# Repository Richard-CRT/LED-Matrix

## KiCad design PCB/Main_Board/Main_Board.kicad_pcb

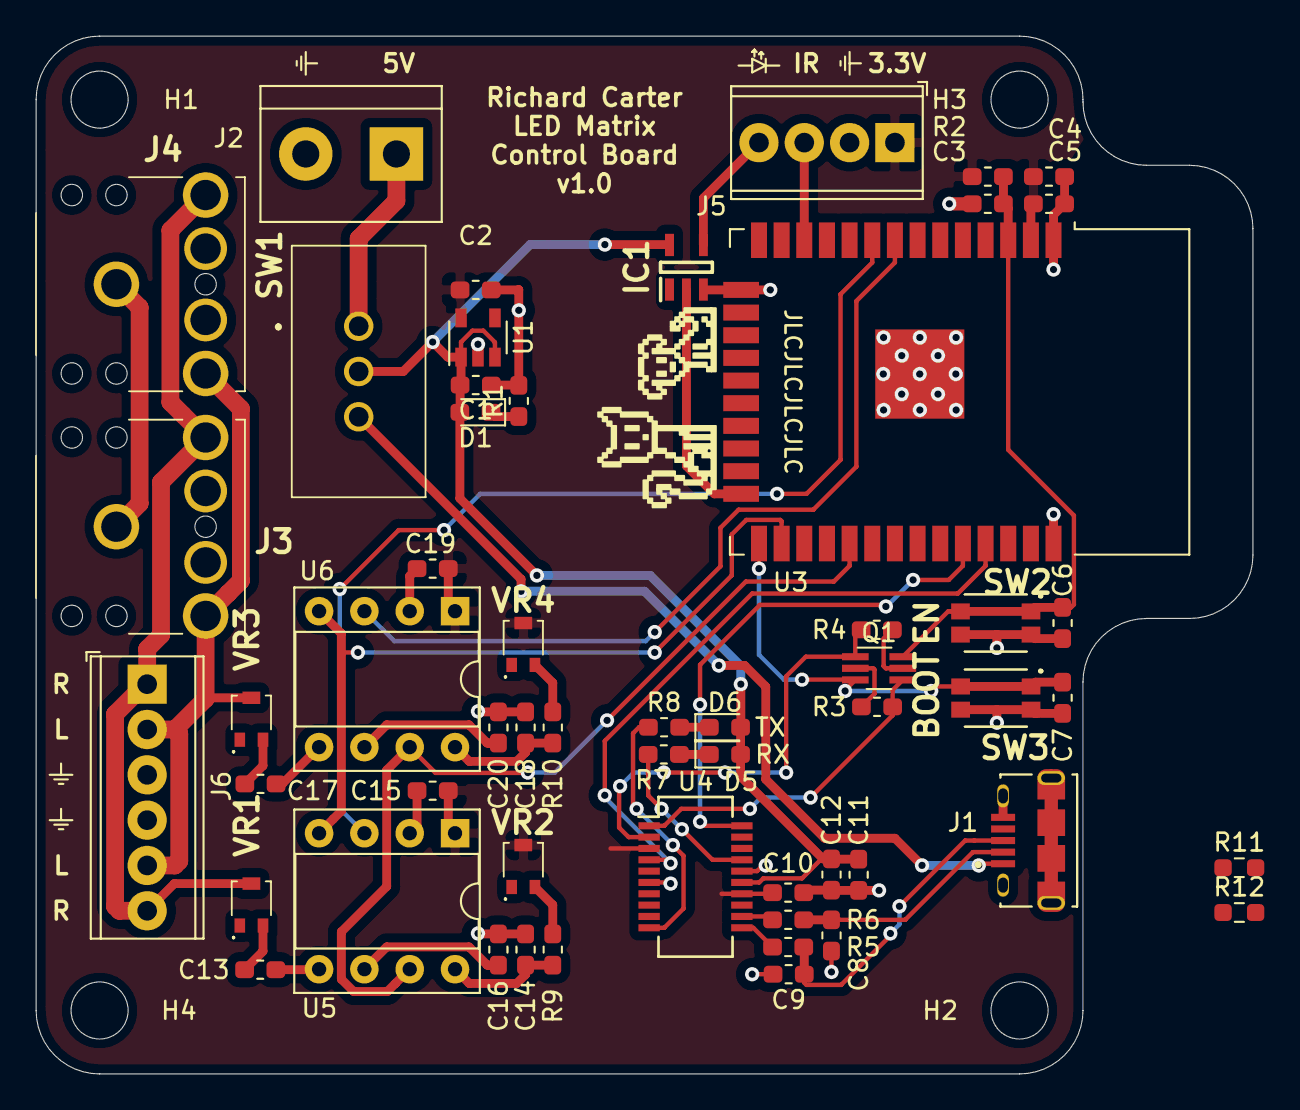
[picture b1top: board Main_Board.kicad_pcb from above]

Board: 2 copper layers, 68.2 x 58.2 mm, 61 parts (0 on the bottom side), 43 nets.

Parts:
ART1: Artwork; dog_2_small
ART2: Artwork; cat_small_mirrored
C1, C2, C3: 10uF; C_0603_1608Metric_Pad1.05x0.95mm_HandSolder
C4: 22uF; C_0603_1608Metric_Pad1.05x0.95mm_HandSolder
C5, C6, C7, C10, C11, C15, C16, C19, C20: 0.1uF; C_0603_1608Metric_Pad1.05x0.95mm_HandSolder
C8, C9: 47pF; C_0603_1608Metric_Pad1.05x0.95mm_HandSolder
C12: 4.7uF; C_0603_1608Metric_Pad1.05x0.95mm_HandSolder
C13, C17: 10nF; C_0603_1608Metric_Pad1.05x0.95mm_HandSolder
C14, C18: 33pF; C_0603_1608Metric_Pad1.05x0.95mm_HandSolder
D1: 5V_LED; LED_0603_1608Metric_Pad1.05x0.95mm_HandSolder
D5: RX_LED; LED_0603_1608Metric_Pad1.05x0.95mm_HandSolder
D6: TX_LED; LED_0603_1608Metric_Pad1.05x0.95mm_HandSolder
H1, H2, H3, H4: MountingHole; MountingHole_3.2mm_M3
IC1: 74LV1T34GVH; SOT95P275X110-5N
J1: USB_B_Micro; AMPHENOL_10118194-0001LF
J2: Screw_Terminal_01x02; TerminalBlock_bornier-2_P5.08mm
J3, J4: SJ1-3523N; SJ13523N
J5: Screw_Terminal_01x04; TerminalBlock_Phoenix_MPT-0,5-4-2.54_1x04_P2.54mm_Horizontal
J6: Screw_Terminal_01x06; TerminalBlock_Phoenix_MPT-0,5-6-2.54_1x06_P2.54mm_Horizontal
Q1: MBT3904DW1; SOT-363_SC-70-6_Handsoldering
R1, R7, R8: CUR_LIMIT_220R; R_0603_1608Metric_Pad1.05x0.95mm_HandSolder
R2: 47k; R_0603_1608Metric_Pad1.05x0.95mm_HandSolder
R3, R4: 10k; R_0603_1608Metric_Pad1.05x0.95mm_HandSolder
R5, R6: 27R; R_0603_1608Metric_Pad1.05x0.95mm_HandSolder
R9, R10: 180k; R_0603_1608Metric_Pad1.05x0.95mm_HandSolder
R11, R12: 1k; R_0603_1608Metric_Pad0.98x0.95mm_HandSolder
SW1: SW_SPDT; 25136NAH
SW2: EN; SKTHAHE010
SW3: BOOT; SKTHAHE010
U1: TLV75533PDBV; SOT-23-5
U3: ESP32-WROOM-32
U4: FT231XS; SSOP-20_3.9x8.7mm_P0.635mm
U5, U6: MSGEQ7; DIP-8_W7.62mm_Socket
VR1, VR2, VR3, VR4: TC42X-2-503E; TC42X2503E

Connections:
/+3.3V: C2.1, C4.1, C5.1, C10.2, C15.1, C19.1, J5.1, R2.1, U1.5, U3.2, U4.3, U4.14, U5.1, U6.1, VR2.2, VR4.2
/+5V: C1.1, C11.1, C12.1, D1.2, D5.2, D6.2, IC1.5, SW1.2, U1.1, U1.3, U4.15
/+POW_5V: J2.1, SW1.1
/+USB_5V: J1.1, SW1.3
/AUDIO_L: J3.2, J4.2, J6.2, J6.5, VR3.2
/AUDIO_R: J3.3, J4.3, J6.1, J6.6, VR1.2
/D+: C9.1, J1.3, R5.2
/D-: C8.1, J1.2, R6.2
/ESP32_Circuit/EN: C3.2, C6.1, Q1.6, R2.2, SW2.1, U3.3
/ESP32_Circuit/IO0: C7.1, Q1.3, SW3.1, U3.25
/ESP32_Circuit/IO1_TXD0: R12.2, U3.35
/ESP32_Circuit/IO3_RXD0: R11.2, U3.34
/ESP32_Circuit/~DTR: Q1.4, R3.2, U4.1
/ESP32_Circuit/~RTS: Q1.1, R4.2, U4.2
/IR_SENSOR: J5.3, U3.12
/LED_OUT_3.3V: IC1.2, U3.24
/LED_OUT_5V: IC1.4, J5.4
/MSGEQ7_L_OUT: U3.8, U6.3
/MSGEQ7_RESET: U3.29, U5.7, U6.7
/MSGEQ7_R_OUT: U3.9, U5.3
/MSGEQ7_STROBE: U3.26, U5.4, U6.4
Earth: C1.2, C2.2, C3.1, C4.2, C5.2, C6.2, C7.2, C8.2, C9.2, C10.1, C11.2, C12.2, C14.2, C15.2, C16.2, C18.2, C19.2, C20.2, IC1.3, J1.5, J1.6, J2.2, J3.1, J4.1, J5.2, J6.3, J6.4, R1.2, SW2.2, SW3.2, U1.2, U3.1, U3.15, U3.38, U3.39, U4.6, U4.16, U5.2, U6.2
unnamed: C13.1, VR1.3
unnamed: C13.2, U5.5
unnamed: C14.1, R9.2, U5.8
unnamed: C16.1, U5.6
unnamed: C17.1, VR3.3
unnamed: C17.2, U6.5
unnamed: C18.1, R10.2, U6.8
unnamed: C20.1, U6.6
unnamed: D1.1, R1.1
unnamed: D5.1, R7.1
unnamed: D6.1, R8.1
unnamed: Q1.2, R3.1
unnamed: Q1.5, R4.1
unnamed: R5.1, U4.11
unnamed: R6.1, U4.12
unnamed: R7.2, U4.17
unnamed: R8.2, U4.10
unnamed: R9.1, VR2.3
unnamed: R10.1, VR4.3
unnamed: R11.1, U4.20
unnamed: R12.1, U4.4

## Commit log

2020-09-06 Added PCB project
2020-09-06 Add schematic
2020-09-06 Restructure file system
2020-09-06 Add IR circuit
2020-09-07 Further schematic work and footprint association
2020-09-07 Further sourcing on mouser
2020-09-08 PCB Layout work
2020-09-08 Add level shifter and further PCB work
2020-09-08 Finish PCB, add missing models, change switch
2020-09-09 Move references and change renders
2020-09-09 Fix plane routing and change dog icon
2020-09-09 Add new art and JLC order number under ESP32-WROOM-32
2020-09-09 Move JLC order number
2020-09-10 Change buttons, make board more compact, add extra mounting hole
2020-09-10 Updated renders
2020-09-10 Moved some references
2020-09-10 Move indicator LED to 5V and increase indicator LED resistors
2020-09-10 Update ground pour timestamps
2020-09-17 Update gitignore
2020-10-01 Add source boilerplate
2020-10-03 Improve circuit
2020-10-03 Add & test hue pattern
2020-10-04 Add IR remote and snake
2020-10-04 Add fade tail snake effect
2020-10-05 Continue development of snake
2020-10-07 Add snake difficulty indicators
2020-10-07 Update ESP32 Module circuit
2020-10-07 Improve map from difficulty to millisecond delay
2020-10-07 Make first apple randomly placed
2020-10-08 Add modes and mode navigation, and improve snake difficulty selection
2020-10-09 Annotate resistors
2020-10-09 Remove redundant file
2020-10-09 Update KiCAD to 5.1.7 and change a couple of footprints
2020-10-10 Audio Equaliser mode
2020-10-10 Add remote control to audio mode
